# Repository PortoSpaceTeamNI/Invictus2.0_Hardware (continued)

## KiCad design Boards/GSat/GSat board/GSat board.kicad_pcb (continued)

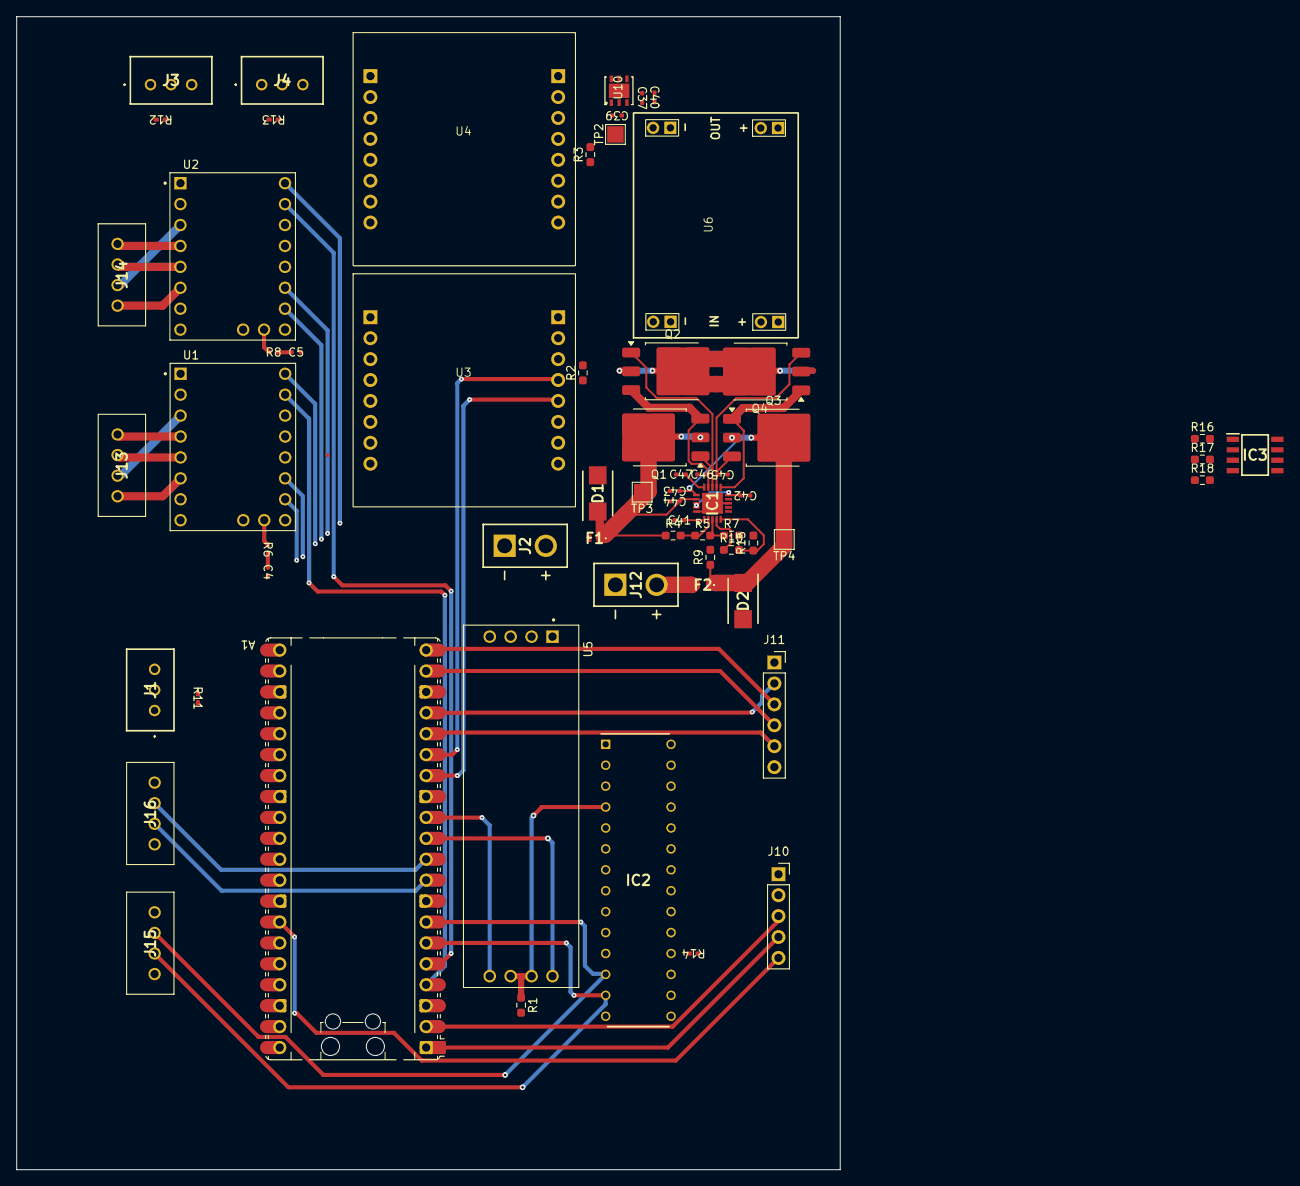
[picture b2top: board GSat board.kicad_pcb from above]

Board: 2 copper layers, 100.0 x 140.0 mm, 63 parts (0 on the bottom side), 74 nets.

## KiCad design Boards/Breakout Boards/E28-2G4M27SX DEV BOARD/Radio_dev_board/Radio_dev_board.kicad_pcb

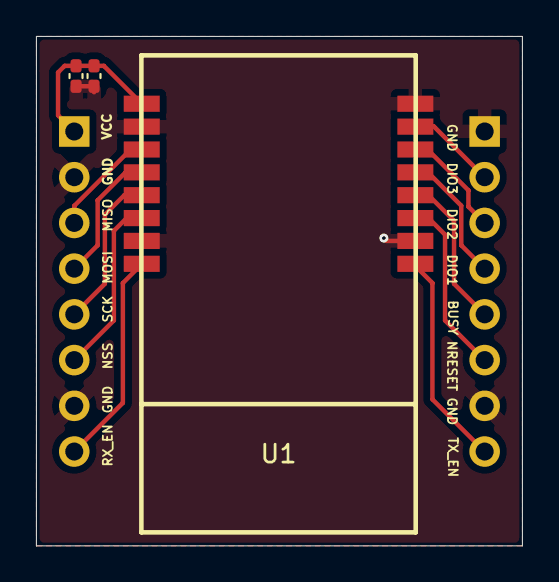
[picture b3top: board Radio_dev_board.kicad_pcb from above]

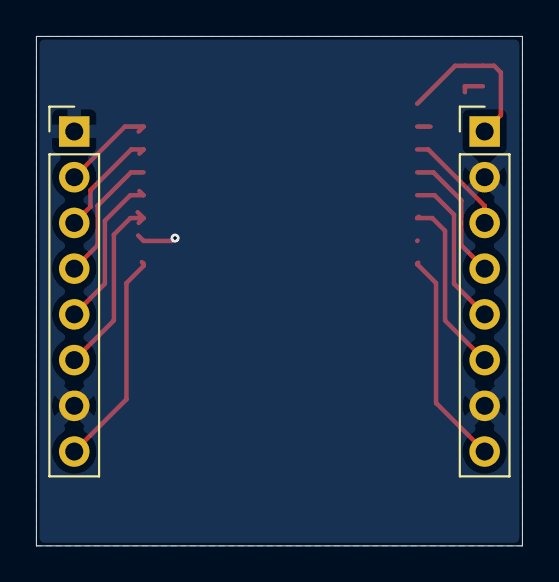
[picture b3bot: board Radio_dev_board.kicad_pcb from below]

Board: 2 copper layers, 27.0 x 28.3 mm, 5 parts (2 on the bottom side), 13 nets.

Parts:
C1: 0.1uF; C_0402_1005Metric_Pad0.74x0.62mm_HandSolder
C2: 100uF; C_0402_1005Metric_Pad0.74x0.62mm_HandSolder
J1, J2: Conn_01x08_Pin; PinHeader_1x08_P2.54mm_Vertical
U1: E28-2G4M27SX; E28-2G4M27S

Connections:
GND: C1.2, C2.2, J1.2, J1.7, J2.10 (Pin_7), J2.16 (Pin_1), U1.2 (GND), U1.7 (GND), U1.10 (GND), U1.16 (GND)
unnamed: J1.3, U1.3 (MISO_TX)
unnamed: J1.4, U1.4 (MOSI_RX)
unnamed: J1.5, U1.5 (SCK_RTSN)
unnamed: J1.6, U1.6 (NSS_CTS)
unnamed: J1.8, U1.8 (RX_EN)
unnamed: J2.15 (Pin_2), U1.15 (DIO3)
unnamed: J2.14 (Pin_3), U1.14 (DIO2)
unnamed: J2.13 (Pin_4), U1.13 (DIO1)
unnamed: J2.12 (Pin_5), U1.12 (BUSY)
unnamed: J2.11 (Pin_6), U1.11 (NRESET)
unnamed: J2.9 (Pin_8), U1.9 (TX_EN)
VCC: C1.1, C2.1, J1.1, U1.1 (VCC)

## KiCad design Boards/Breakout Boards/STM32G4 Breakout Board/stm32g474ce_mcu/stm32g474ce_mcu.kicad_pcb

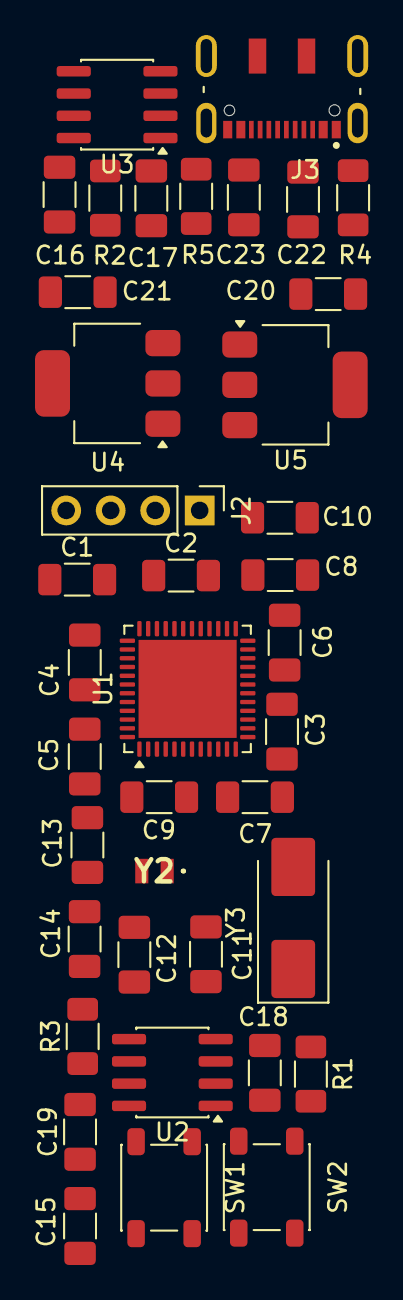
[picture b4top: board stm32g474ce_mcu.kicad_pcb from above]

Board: 2 copper layers, 39 parts (0 on the bottom side), 21 nets, no tracks yet.

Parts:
C1, C2, C3, C5, C8: 100n; C_1206_3216Metric_Pad1.33x1.80mm_HandSolder
C4: 4.7u; C_1206_3216Metric_Pad1.33x1.80mm_HandSolder
C6: 10n; C_1206_3216Metric_Pad1.33x1.80mm_HandSolder
C7, C9, C10: 1u; C_1206_3216Metric_Pad1.33x1.80mm_HandSolder
C11, C12: 9p; C_1206_3216Metric_Pad1.33x1.80mm_HandSolder
C13, C14: 3.5p; C_1206_3216Metric_Pad1.33x1.80mm_HandSolder
C15, C16, C17, C18, C19: 0.1u; C_1206_3216Metric_Pad1.33x1.80mm_HandSolder
C20, C22: 10u; C_1206_3216Metric_Pad1.33x1.80mm_HandSolder
C21: 22u; C_1206_3216Metric_Pad1.33x1.80mm_HandSolder
C23: 28u; C_1206_3216Metric_Pad1.33x1.80mm_HandSolder
J2: Conn_01x04_Pin; PinHeader_1x04_P2.54mm_Vertical
J3: DX07S016JA1R1500; JAE_DX07S016JA1R1500
R1: 10k; R_1206_3216Metric_Pad1.30x1.75mm_HandSolder
R2, R3: 120; R_1206_3216Metric_Pad1.30x1.75mm_HandSolder
R4, R5: 5k1; R_1206_3216Metric_Pad1.30x1.75mm_HandSolder
SW1: RESET; SW_SPST_PTS647_Sx38
SW2: SW_SPDT; SW_SPST_PTS647_Sx38
U1: STM32G473CEUx; QFN-48-1EP_7x7mm_P0.5mm_EP5.6x5.6mm
U2, U3: MCP2562FDT; SOIC-8_3.9x4.9mm_P1.27mm
U4: AMS1117-3.3; SOT-223-3_TabPin2
U5: AMS1117-5.0; SOT-223-3_TabPin2
Y2: 3.768k; ABS06-32Khz
Y3: 8Mhz; Crystal_SMD_0603-2Pin_6.0x3.5mm_HandSoldering

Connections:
+3.3V: C1.1, C2.1, C3.1, C4.1, C5.1, C6.1, C7.1, C8.1, C9.1, C10.1, C16.2, C19.2, C21.1, J2.1, U1.1 (VBAT), U1.20 (VREF+), U1.21 (VDDA), U1.23 (VDD), U1.35 (VDD), U1.48 (VDD), U2.5 (Vio), U3.5 (Vio), U4.2 (VO)
+5V: C17.1, C18.1, C20.1, C23.1, U2.3 (VDD), U3.3 (VDD), U4.3 (VI), U5.2 (VO)
/BOOT0: R1.2, U1.46 (PB8)
/OSC32_IN: C14.2, U1.3 (PC14), Y2.2
/OSC32_OUT: C13.2, U1.4 (PC15), Y2.1
/OSC_IN: C11.2, U1.5 (PF0), Y3.2
/OSC_OUT: C12.2, U1.6 (PF1), Y3.1
/SWCLK: J2.3, U1.37 (PA14)
/SWDIO: J2.2, U1.36 (PA13)
FDCAN2_RX: U1.43 (PB5), U3.4 (RXD)
FDCAN2_TX: U1.44 (PB6), U3.1 (TXD)
FDCAN3_RX: U1.41 (PB3), U2.4 (RXD)
FDCAN3_TX: U1.42 (PB4), U2.1 (TXD)
GND: C1.2, C2.2, C3.2, C4.2, C5.2, C6.2, C7.2, C8.2, C9.2, C10.2, C11.1, C12.1, C13.1, C14.1, C15.2, C16.1, C17.2, C18.2, C19.1, C20.2, C21.2, C22.2, C23.2, J2.4, J3.1 (GND), J3.12 (GND), R4.1, R5.1, SW1.2, SW2.1 (A), U1.49 (VSS), U2.2 (VSS), U2.8 (STBY), U3.2 (VSS), U3.8 (STBY), U4.1 (GND), U5.1 (GND)
NRST: C15.1, SW1.1, U1.7 (PG10)
unnamed: J3.3 (CC1), R4.2
unnamed: J3.9 (CC2), R5.2
unnamed: R1.1, SW2.2 (B)
USB_D+: J3.6 (D+), J3.7 (D+), U1.34 (PA12)
USB_D-: J3.5 (D-), J3.8 (D-), U1.33 (PA11)
VBUS: C22.1, J3.2 (VBUS), J3.11 (VBUS), U5.3 (VI)

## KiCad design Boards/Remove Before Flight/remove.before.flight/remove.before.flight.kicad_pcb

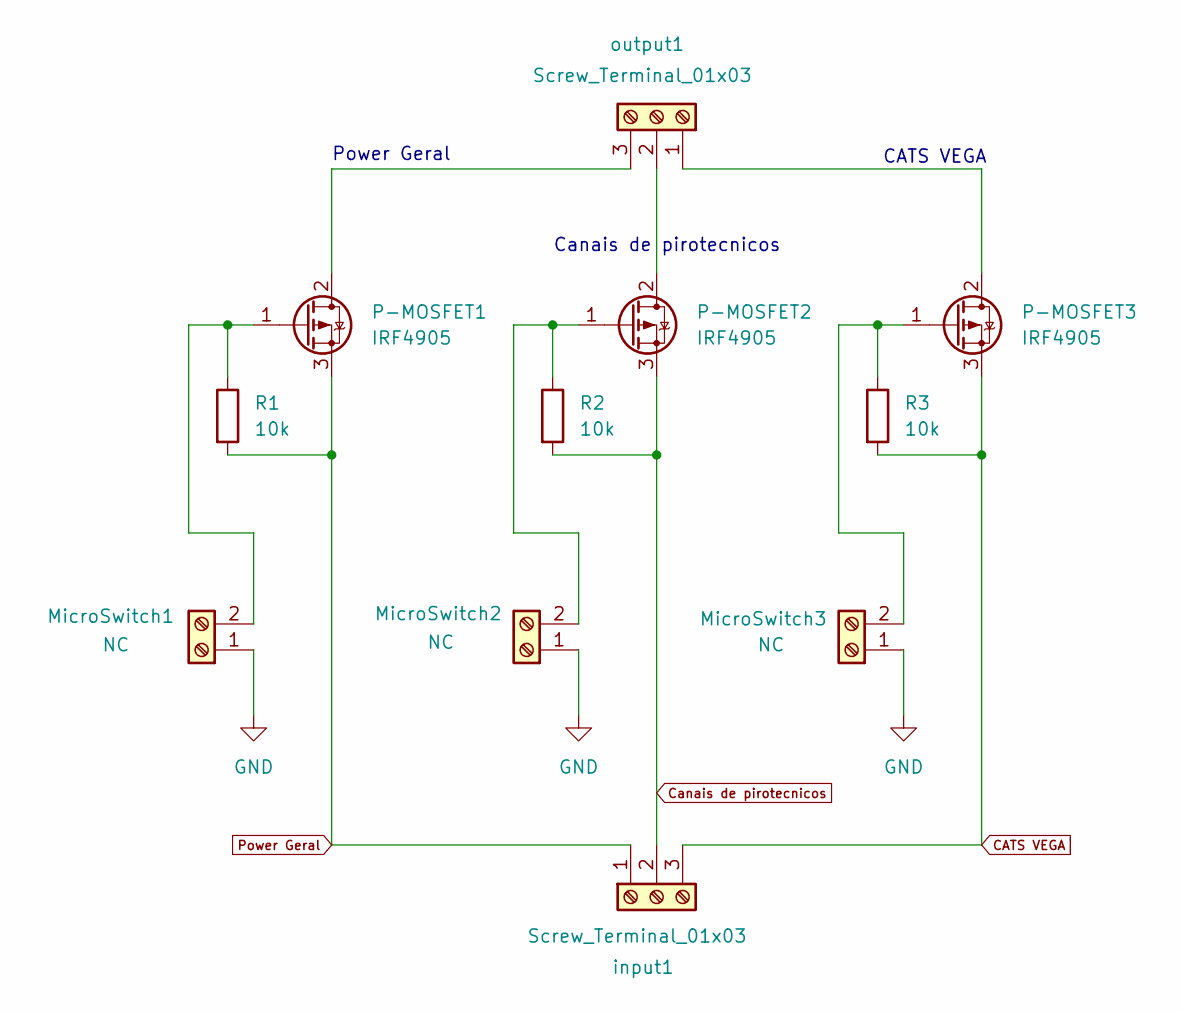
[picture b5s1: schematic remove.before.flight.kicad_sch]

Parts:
MicroSwitch1, MicroSwitch2, MicroSwitch3: NC; TerminalBlock_Xinya_XY308-2.54-2P_1x02_P2.54mm_Horizontal
P-MOSFET1, P-MOSFET2, P-MOSFET3: IRF4905; TO-220-3_Vertical
R1, R2, R3: 10k; R_Axial_DIN0207_L6.3mm_D2.5mm_P10.16mm_Horizontal
input1: Screw_Terminal_01x03; TerminalBlock_Xinya_XY308-2.54-3P_1x03_P2.54mm_Horizontal
output1: Screw_Terminal_01x03; TerminalBlock_Xinya_XY308-2.54-3P_1x03_P2.54mm_Horizontal

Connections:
CATS VEGA: P-MOSFET3.3 (S), R3.2, input1.3
Canais de pirotecnicos: P-MOSFET2.3 (S), R2.2, input1.2
GND: MicroSwitch1.1, MicroSwitch2.1, MicroSwitch3.1
unnamed: MicroSwitch1.2, P-MOSFET1.1 (G), R1.1
unnamed: MicroSwitch2.2, P-MOSFET2.1 (G), R2.1
unnamed: MicroSwitch3.2, P-MOSFET3.1 (G), R3.1
unnamed: P-MOSFET1.2 (D), output1.3
unnamed: P-MOSFET2.2 (D), output1.2
unnamed: P-MOSFET3.2 (D), output1.1
Power Geral: P-MOSFET1.3 (S), R1.2, input1.1

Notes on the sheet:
CATS VEGA
Power Geral
Canais de pirotecnicos

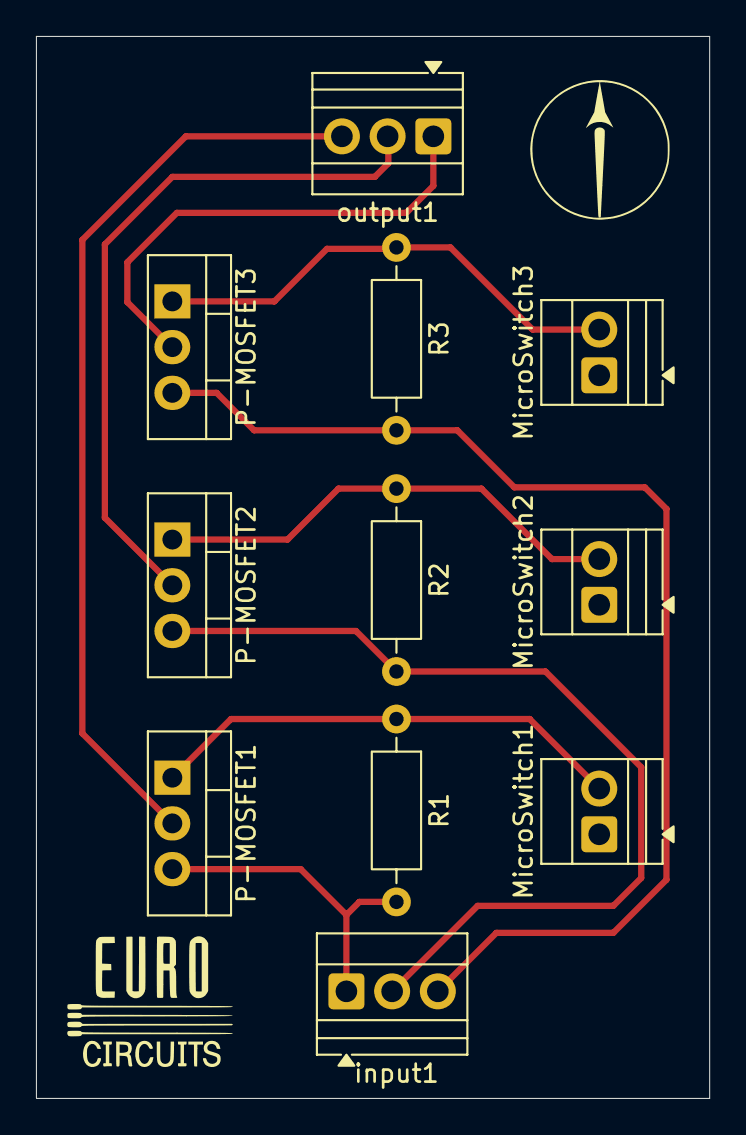
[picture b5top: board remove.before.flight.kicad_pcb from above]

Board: 2 copper layers, 37.4 x 59.0 mm, 11 parts (0 on the bottom side), 10 nets.

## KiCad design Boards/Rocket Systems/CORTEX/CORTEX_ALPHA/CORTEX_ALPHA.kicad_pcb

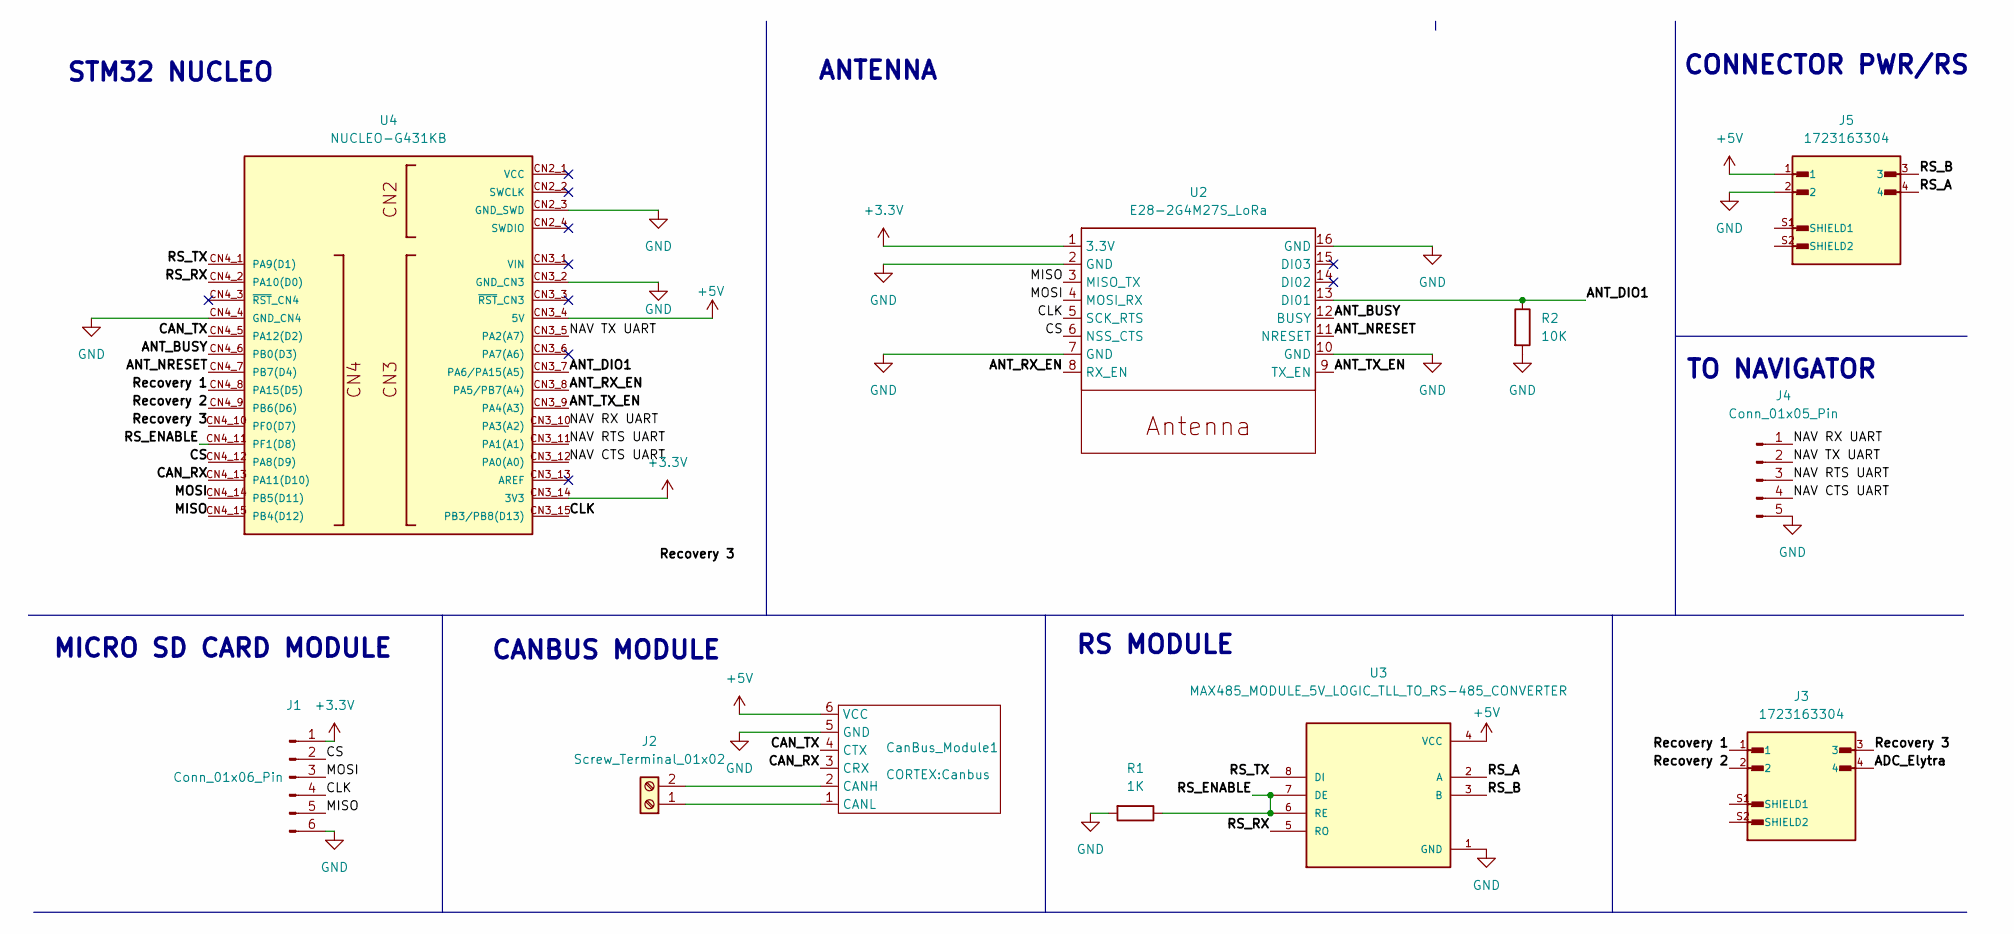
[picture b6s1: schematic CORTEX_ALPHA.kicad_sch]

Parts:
CanBus_Module1: Canbus
J1: Conn_01x06_Pin; PinSocket_1x06_P2.54mm_Vertical
J2: Screw_Terminal_01x02; TerminalBlock_Xinya_XY308-2.54-2P_1x02_P2.54mm_Horizontal
J3, J5: 1723163304; MOLEX_1723163304; PARTREV D
J4: Conn_01x05_Pin; PinHeader_1x05_P2.54mm_Vertical
R1: 1K; R_0603_1608Metric_Pad0.98x0.95mm_HandSolder
R2: 10K; R_0603_1608Metric_Pad0.98x0.95mm_HandSolder
U2: E28-2G4M27S_LoRa; Radio_Module_PST
U3: MAX485_MODULE_5V_LOGIC_TLL_TO_RS-485_CONVERTER; MODULE_MAX485_MODULE_5V_LOGIC_TLL_TO_RS-485_CONVERTER; PARTREV 1r0
U4: NUCLEO-G431KB; MODULE_NUCLEO-G431KB; PARTREV 2

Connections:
+3.3V: J1.1, U2.1 (3.3V), U4.CN3_14 (3V3)
+5V: CanBus_Module1.6 (VCC), J5.1, U3.4 (VCC), U4.CN3_4 (5V)
/ADC_Elytra: J3.4
/ANT_BUSY: U2.12 (BUSY), U4.CN4_6 (PB0(D3))
/ANT_DIO1: R2.1, U2.13 (DI01), U4.CN3_7 (PA6/PA15(A5))
/ANT_NRESET: U2.11 (NRESET), U4.CN4_7 (PB7(D4))
/ANT_RX_EN: U2.8 (RX_EN), U4.CN3_8 (PA5/PB7(A4))
/ANT_TX_EN: U2.9 (TX_EN), U4.CN3_9 (PA4(A3))
/CAN_RX: CanBus_Module1.3 (CRX), U4.CN4_13 (PA11(D10))
/CAN_TX: CanBus_Module1.4 (CTX), U4.CN4_5 (PA12(D2))
/CLK: J1.4, U2.5 (SCK_RTS), U4.CN3_15 (PB3/PB8(D13))
/CS: J1.2, U2.6 (NSS_CTS), U4.CN4_12 (PA8(D9))
/MISO: J1.5, U2.3 (MISO_TX), U4.CN4_15 (PB4(D12))
/MOSI: J1.3, U2.4 (MOSI_RX), U4.CN4_14 (PB5(D11))
/NAV CTS UART: J4.4, U4.CN3_12 (PA0(A0))
/NAV RTS UART: J4.3, U4.CN3_11 (PA1(A1))
/NAV RX UART: J4.1, U4.CN3_10 (PA3(A2))
/NAV TX UART: J4.2, U4.CN3_5 (PA2(A7))
/RS_A: J5.4, U3.2 (A)
/RS_B: J5.3, U3.3 (B)
/RS_ENABLE: R1.1, U3.6 (RE), U3.7 (DE), U4.CN4_11 (PF1(D8))
/RS_RX: U3.5 (RO), U4.CN4_2 (PA10(D0))
/RS_TX: U3.8 (DI), U4.CN4_1 (PA9(D1))
/Recovery 1: J3.1, U4.CN4_8 (PA15(D5))
/Recovery 2: J3.2, U4.CN4_9 (PB6(D6))
/Recovery 3: J3.3, U4.CN4_10 (PF0(D7))
GND: CanBus_Module1.5 (GND), J1.6, J4.5, J5.2, R1.2, R2.2, U2.2 (GND), U2.7 (GND), U2.10 (GND), U2.16 (GND), U3.1 (GND), U4.CN2_3 (GND_SWD), U4.CN3_2 (GND_CN3), U4.CN4_4 (GND_CN4)
unnamed: CanBus_Module1.2 (CANH), J2.2
unnamed: CanBus_Module1.1 (CANL), J2.1

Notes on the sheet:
STM32 NUCLEO
TO NAVIGATOR
RS MODULE
CANBUS MODULE
CONNECTOR PWR/RS
MICRO SD CARD MODULE
ANTENNA

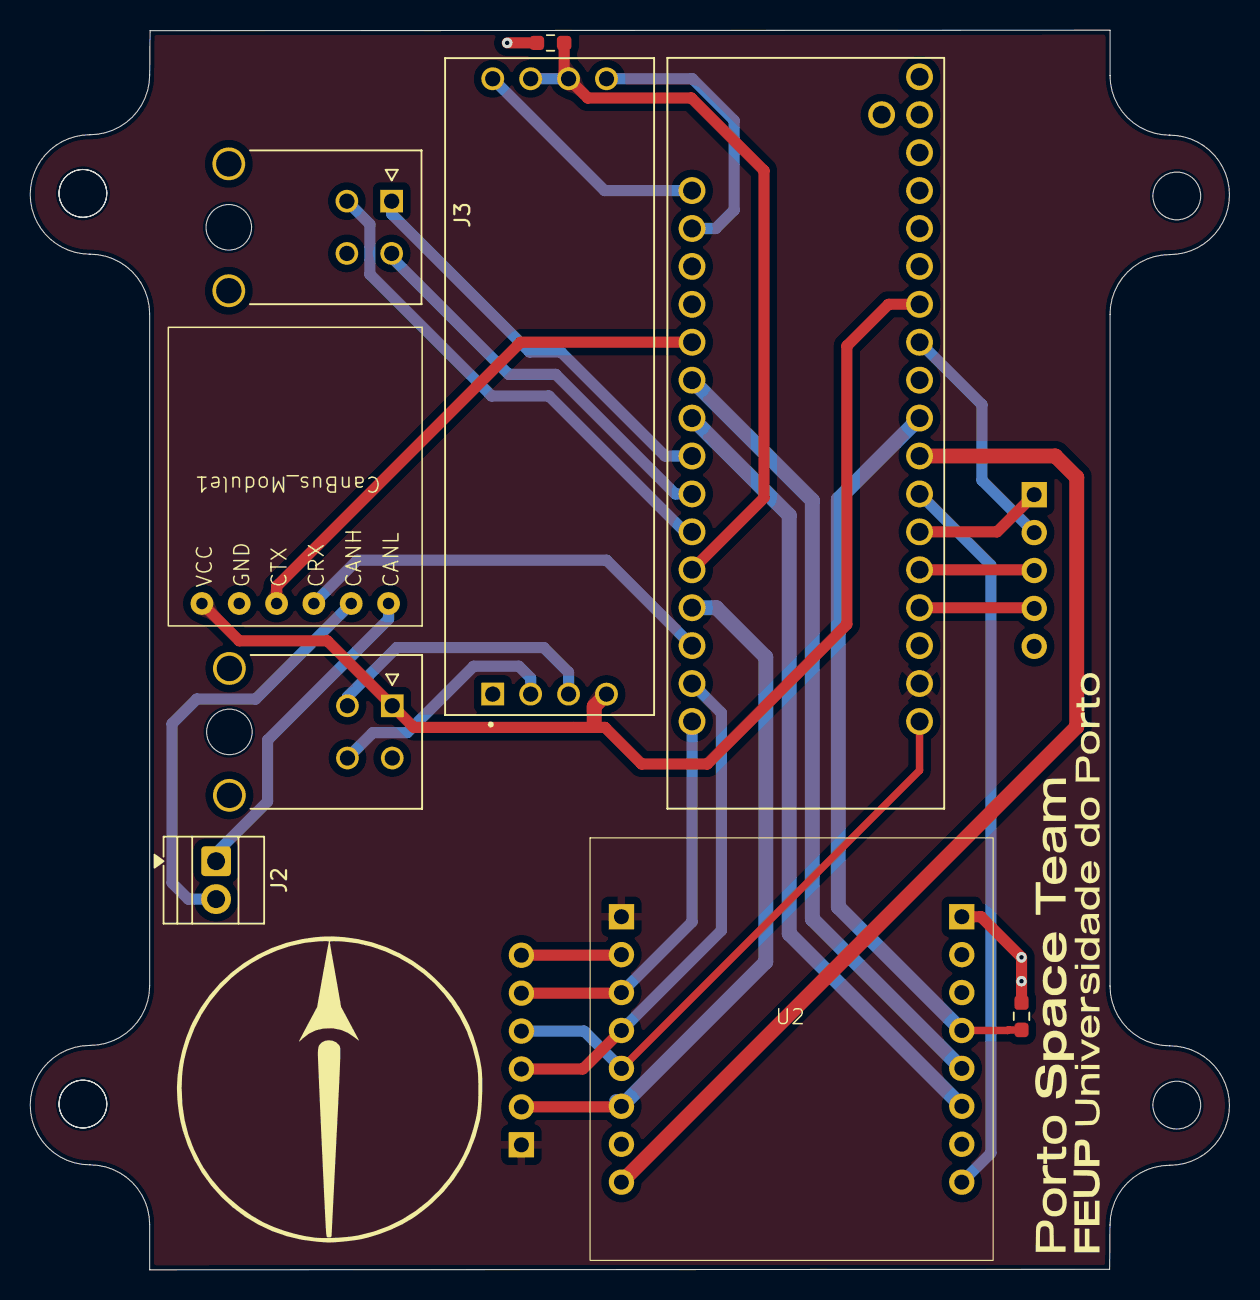
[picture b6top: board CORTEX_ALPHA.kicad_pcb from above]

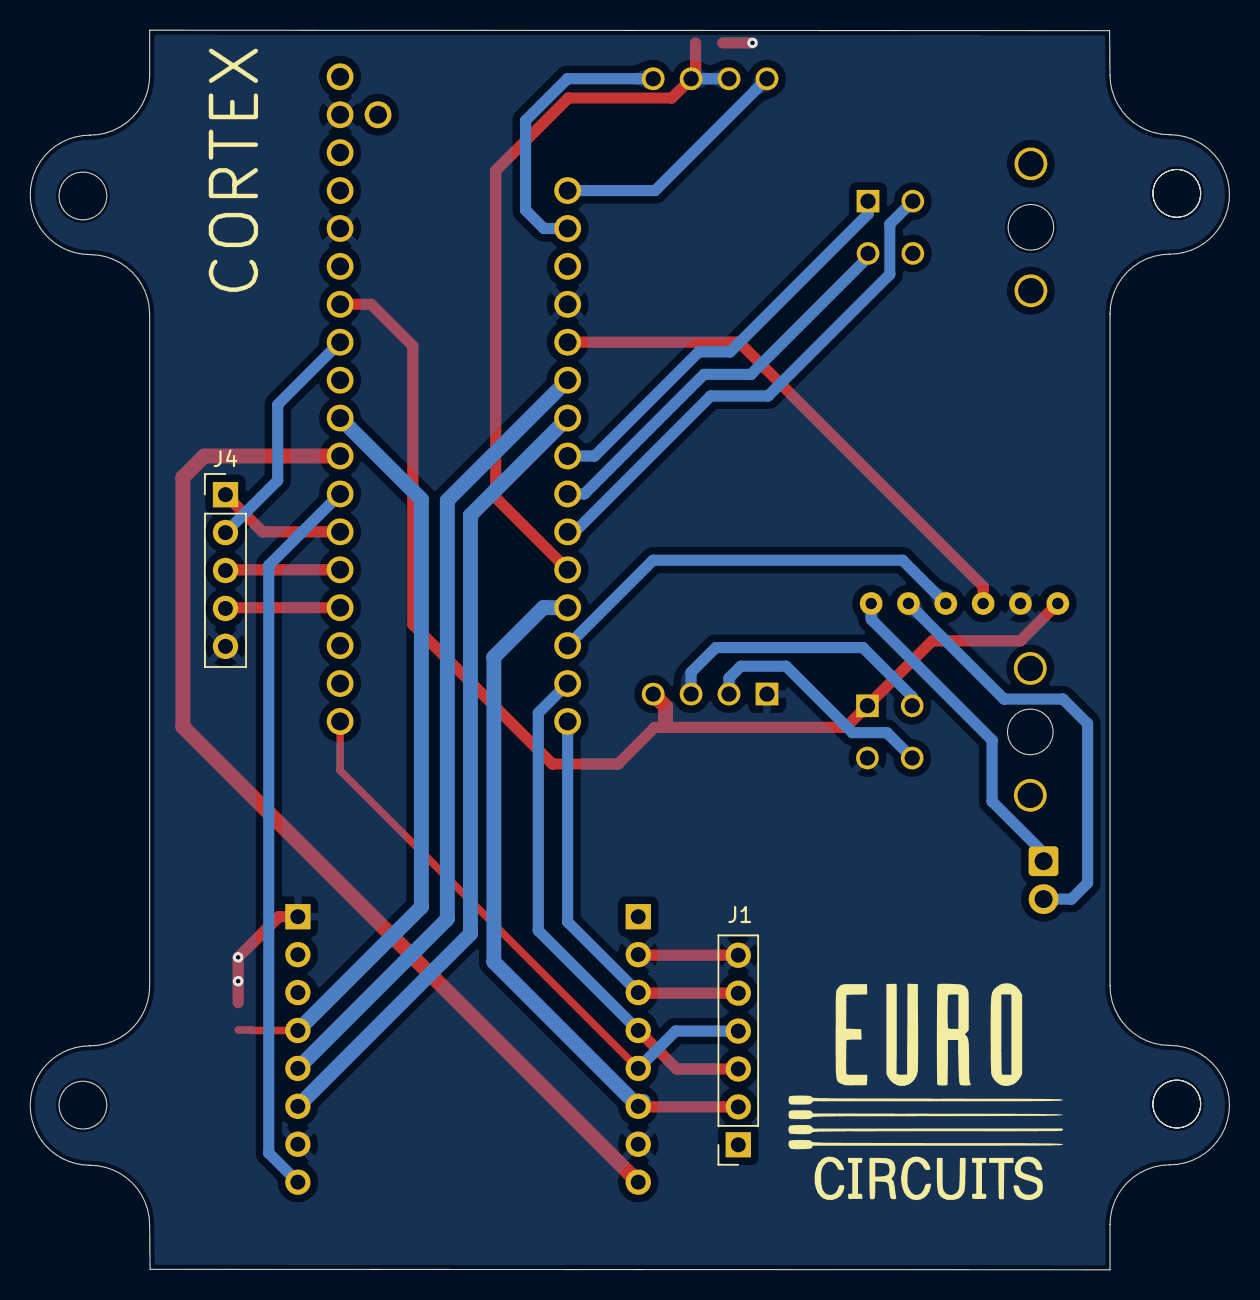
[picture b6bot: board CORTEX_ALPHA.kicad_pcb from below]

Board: 2 copper layers, 80.3 x 83.0 mm, 11 parts (2 on the bottom side), 28 nets.

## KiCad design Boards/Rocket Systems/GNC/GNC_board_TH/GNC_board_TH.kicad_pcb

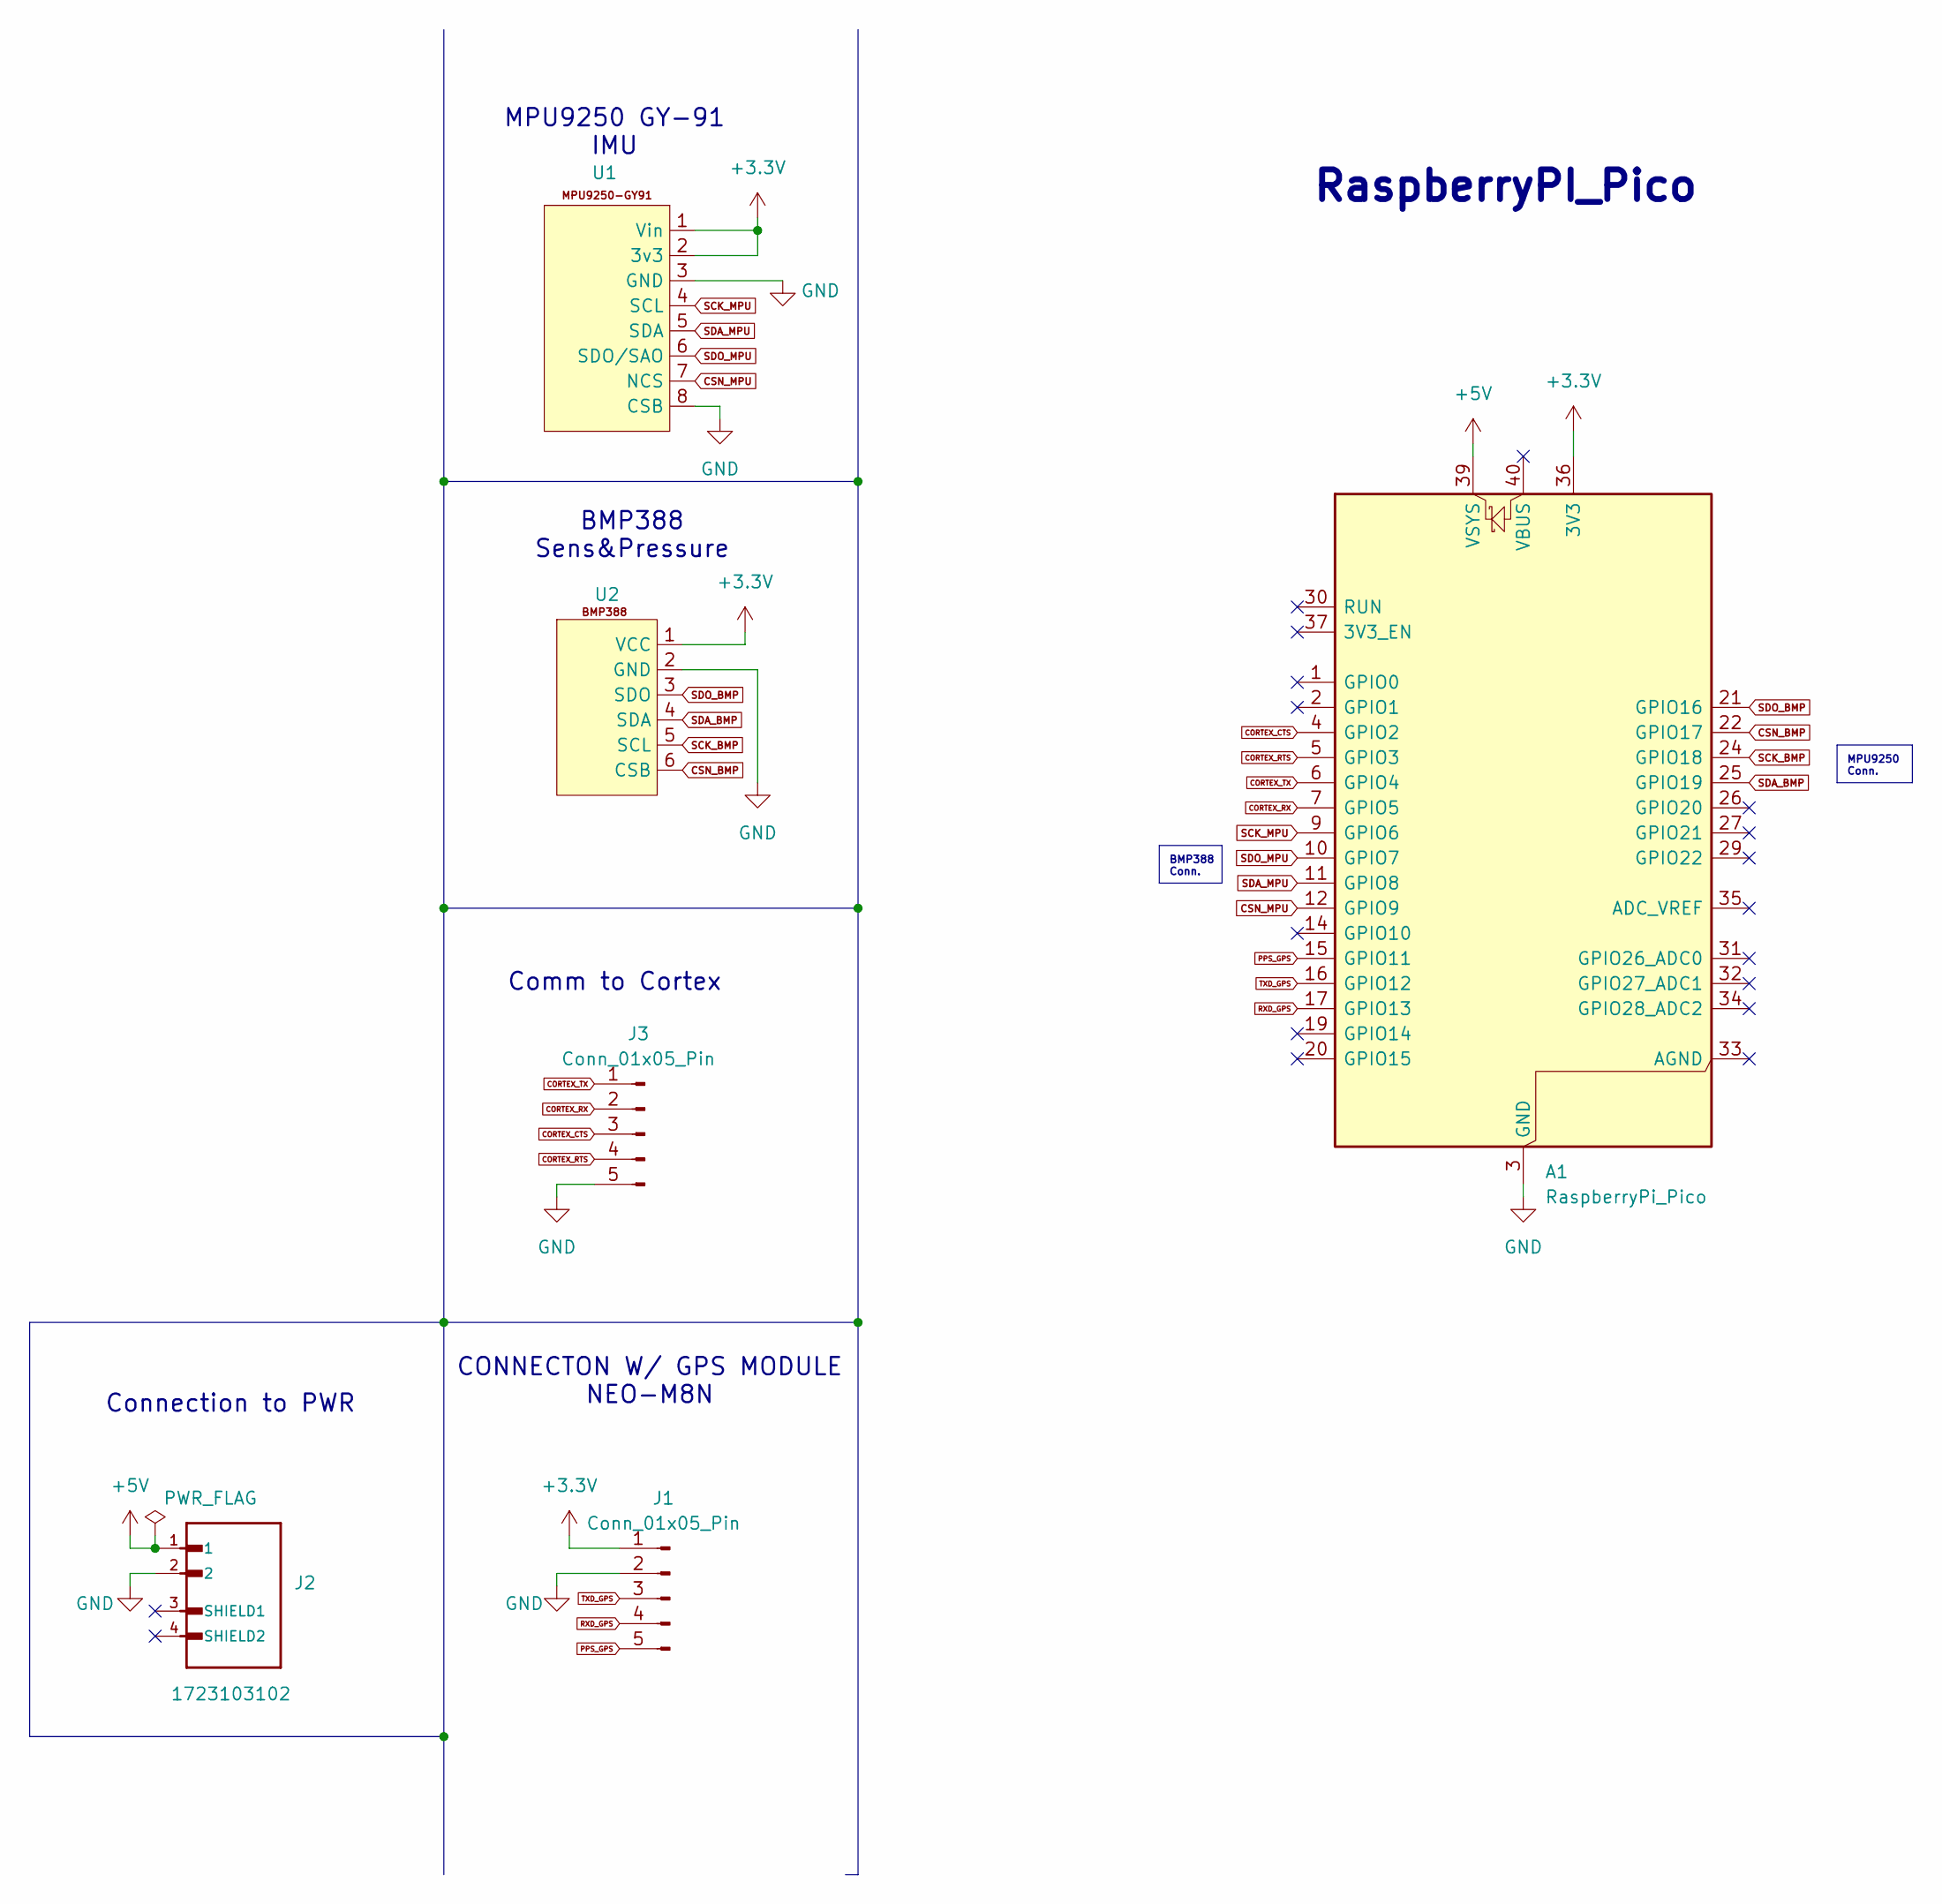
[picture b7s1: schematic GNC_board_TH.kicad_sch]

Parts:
A1: RaspberryPi_Pico; RaspberryPi_Pico_Common_Unspecified
J1, J3: Conn_01x05_Pin; PinSocket_1x05_P2.54mm_Vertical
J2: 1723103102; CONN02_1723103102_MOL; MANUFACTURER_PART_NUMBER 1723103102; DigiKey_Part_Number 900-1723103102-ND
U1: MPU9250
U2: BMP388

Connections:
+3.3V: A1.36 (3V3), J1.1, U1.1 (Vin), U1.2 (3v3), U2.1 (VCC)
+5V: A1.39 (VSYS), J2.1
CORTEX_CTS: A1.4 (GPIO2), J3.3
CORTEX_RTS: A1.5 (GPIO3), J3.4
CORTEX_RX: A1.7 (GPIO5), J3.2
CORTEX_TX: A1.6 (GPIO4), J3.1
CSN_BMP: A1.22 (GPIO17), U2.6 (CSB)
CSN_MPU: A1.12 (GPIO9), U1.7 (NCS)
GND: A1.3 (GND), A1.8 (GND), A1.13 (GND), A1.18 (GND), A1.23 (GND), A1.28 (GND), A1.38 (GND), J1.2, J2.2, J3.5, U1.3 (GND), U1.8 (CSB), U2.2 (GND)
PPS_GPS: A1.15 (GPIO11), J1.5
RXD_GPS: A1.17 (GPIO13), J1.4
SCK_BMP: A1.24 (GPIO18), U2.5 (SCL)
SCK_MPU: A1.9 (GPIO6), U1.4 (SCL)
SDA_BMP: A1.25 (GPIO19), U2.4 (SDA)
SDA_MPU: A1.11 (GPIO8), U1.5 (SDA)
SDO_BMP: A1.21 (GPIO16), U2.3 (SDO)
SDO_MPU: A1.10 (GPIO7), U1.6 (SDO/SAO)
TXD_GPS: A1.16 (GPIO12), J1.3

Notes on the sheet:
MPU9250 GY-91 IMU
RaspberryPI_Pico
BMP388 Sens&Pressure
CONNECTON W/ GPS MODULE NEO-M8N
Comm to Cortex
Connection to PWR
BMP388 Conn.
MPU9250 Conn.

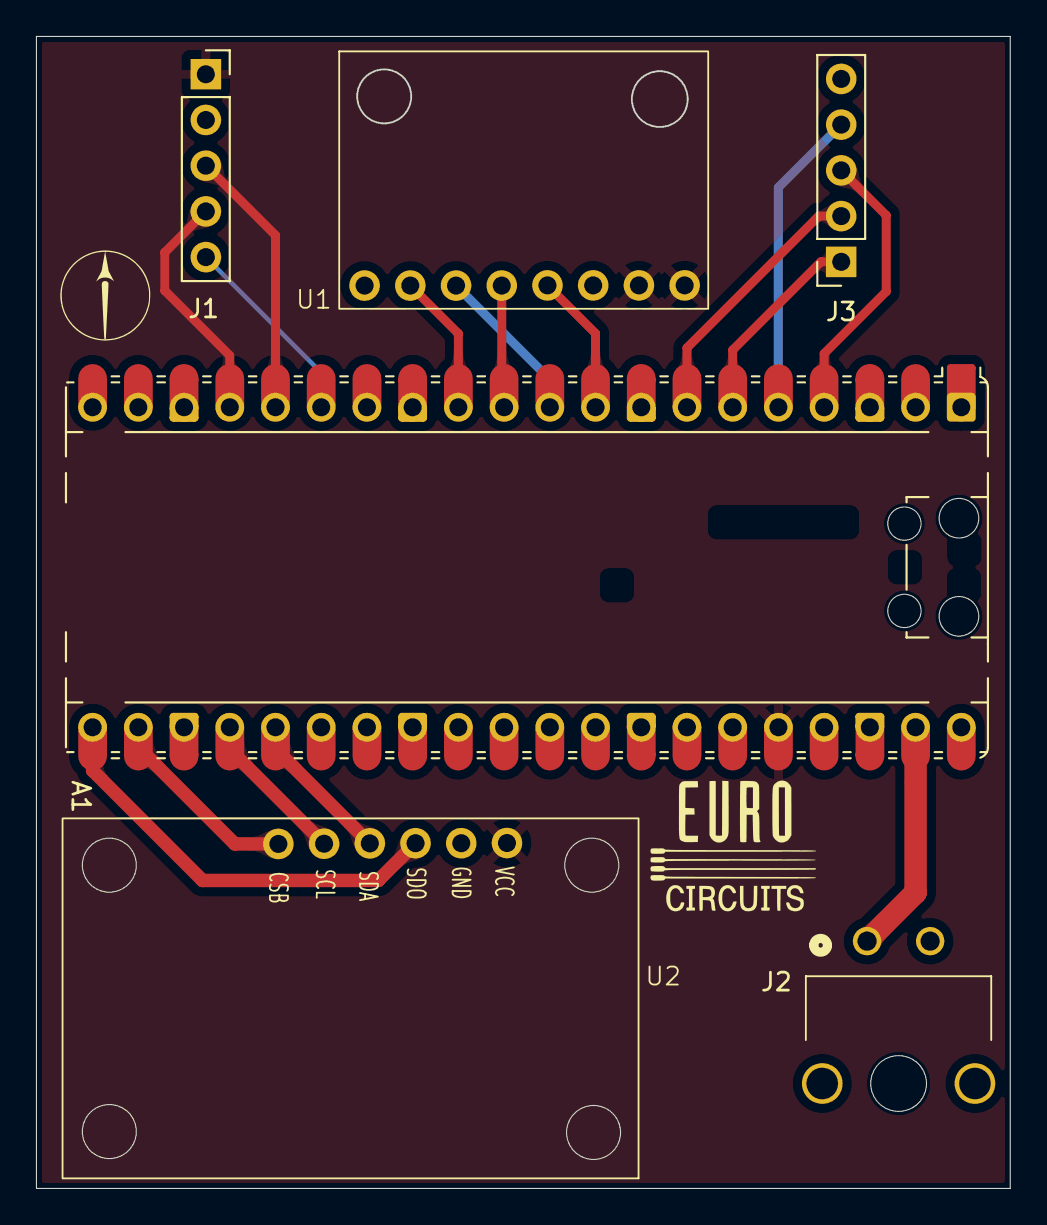
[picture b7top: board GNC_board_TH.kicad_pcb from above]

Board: 2 copper layers, 54.1 x 64.0 mm, 6 parts (0 on the bottom side), 18 nets.
